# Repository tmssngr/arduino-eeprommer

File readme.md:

# Arduino-Shield to flash EEPROMs

This is an Arduino shield that can be used to read or flash EEPROMs.
I've successfully flashed 28C16 and 28C64.

## Hardware
The schematic you can find [here](kicad/EPROM-Shield.pdf).
It has been created with KiCad 5.1.12.

The 74'595 shift registers are used to set the address lines A0-A12, /CS, /OE and /WE.
The address lines A13 and A14 for 28C128 or 28C256 are only available through jumpers, so only up to 8kB could be flashed in one row.

The EEPROMs data pins are connected via resistors to the arduino pins D0-D7 to prevent problems if the EEPROM and the Arduino accessing these pins as output.
For those arduino boards that use pins D0 and D1 for serial communication, you can use AD0 and AD1 instead.
In that case omit the resistors to D0 and D1, install those to AD0 and AD1, and change the constants `PIN_D0` and `PIN_D1` at the beginning of the [Eprommer595.ino](arduino/Eprommer595/Eprommer595.ino).

Note, you need to solder the pin headers onto the bottom side (in contrast to the below 3D view).

## Software
For simplicity the data to flash should be provided as array content (see [data_jute6k_video.h](arduino/Eprommer595/data_jute6k_video.h)).
Any output is provided over serial communication (9600 baud).

## Todo
- reserve more space around EEPROM to be able to mount a ZIF socket

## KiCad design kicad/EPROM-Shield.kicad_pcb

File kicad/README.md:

# EEPROMmer as Arduino Shield
This is my first attempt to create am EEPROMmer in the form of an Arduino shield.

## Alternative Approaches:
- Arduino-Mega-based: https://github.com/bmpc/arduino_eeprom_programmer
- Very good explanation of steps from breadboard: https://www.youtube.com/watch?v=K88pgWhEb1M

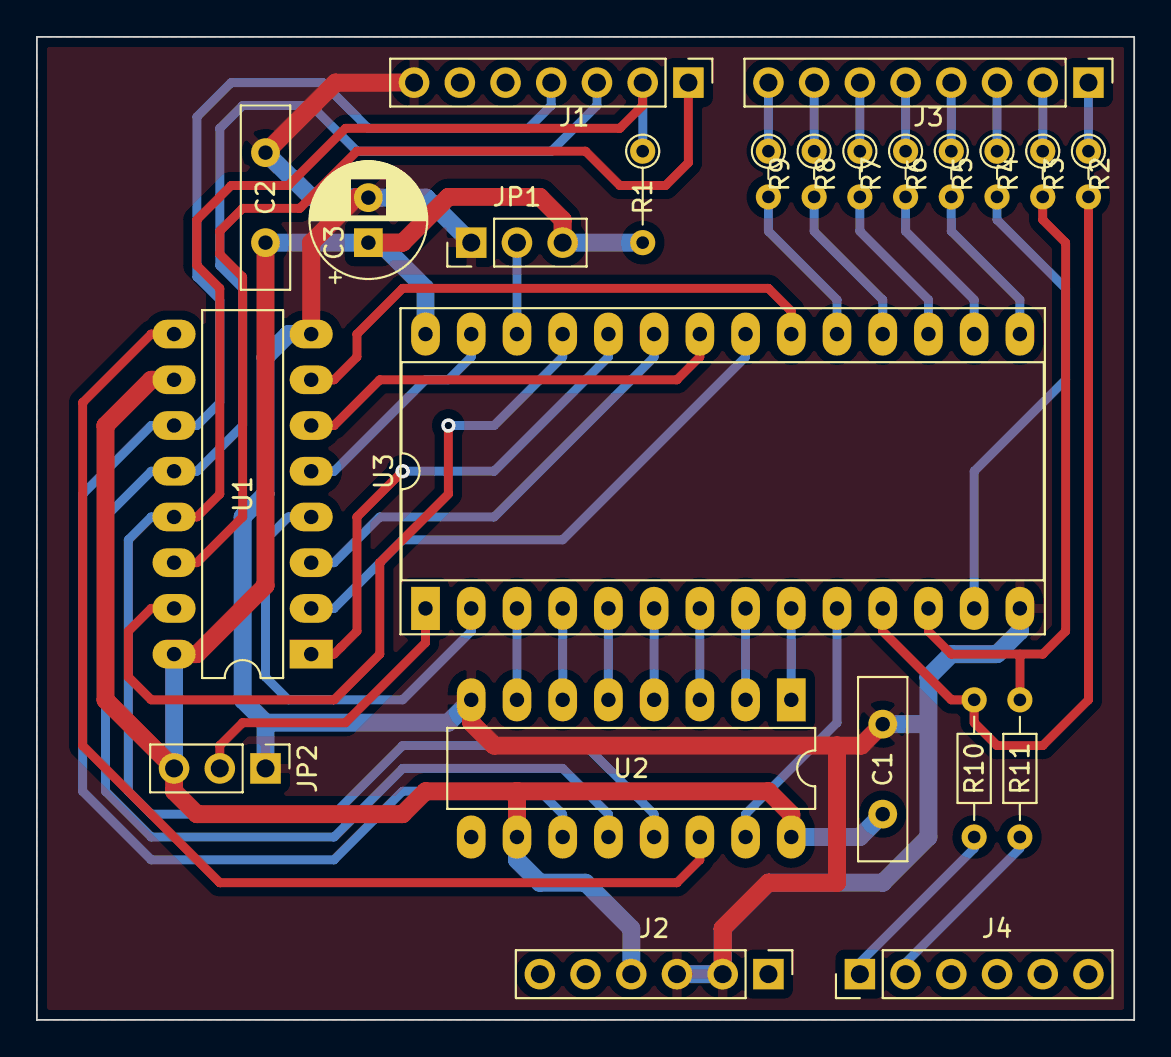
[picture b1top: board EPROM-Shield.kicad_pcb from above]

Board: 2 copper layers, 61.0 x 54.6 mm, 23 parts (0 on the bottom side), 43 nets.

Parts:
C1, C2: 100n; C_Disc_D10.0mm_W2.5mm_P5.00mm
C3: 47u; CP_Radial_D6.3mm_P2.50mm
J1: D8-D13; PinHeader_1x07_P2.54mm_Vertical
J2: Conn_01x06; PinHeader_1x06_P2.54mm_Vertical
J3: D0-D7; PinHeader_1x08_P2.54mm_Vertical
J4: A0-A5; PinHeader_1x06_P2.54mm_Vertical
JP1: A13 1-0; PinHeader_1x03_P2.54mm_Vertical
JP2: A14 1-0; PinHeader_1x03_P2.54mm_Vertical
R1: 10k; R_Axial_DIN0204_L3.6mm_D1.6mm_P5.08mm_Vertical
R2, R3, R4, R5, R6, R7, R8, R9: 510; R_Axial_DIN0204_L3.6mm_D1.6mm_P2.54mm_Vertical
R10, R11: 510; R_Axial_DIN0204_L3.6mm_D1.6mm_P7.62mm_Horizontal
U1, U2: 74LS595; DIP-16_W7.62mm_LongPads
U3: 28C256; DIP-28_W15.24mm_Socket_LongPads

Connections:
/A0: U2.15, U3.10
/A1: U2.1, U3.9
/A2: U2.2, U3.8
/A3: U2.3, U3.7
/A4: U2.4, U3.6
/A5: U2.5, U3.5
/A6: U2.6, U3.4
/A7: U2.7, U3.3
/A8: U1.15, U3.25
/A9: U1.1, U3.24
/A10: U1.2, U3.21
/A11: U1.3, U3.23
/A12: U1.4, U3.2
/A13: JP1.2, U3.26
/A14: JP2.2, U3.1
/AD0: J4.1, R10.1
/AD1: J4.2, R11.1
/CS: U1.7, U3.20
/D0: J3.1, R2.1
/D1: J3.2, R3.1
/D2: J3.3, R4.1
/D3: J3.4, R5.1
/D4: J3.5, R6.1
/D5: J3.6, R7.1
/D6: J3.7, R8.1
/D7: J3.8, R9.1
/OE: U1.6, U3.22
/RCLK: J1.3, U1.12, U2.12
/SER: J1.1, U1.14
/SERCLK: J1.4, U1.11, U2.11
/WE: U1.5, U3.27
/_OE: J1.2, R1.1, U1.13, U2.13
GND: C1.2, C2.2, C3.2, J1.7, J2.2, J2.3, JP1.1, JP2.1, U1.8, U2.8, U3.14
unnamed: R4.2, U3.13
unnamed: R5.2, U3.15
unnamed: R6.2, U3.16
unnamed: R7.2, U3.17
unnamed: R8.2, U3.18
unnamed: R9.2, U3.19
unnamed: R2.2, R10.2, U3.11
unnamed: R3.2, R11.2, U3.12
unnamed: U1.9, U2.14
VCC: C1.1, C2.1, C3.1, J2.4, JP1.3, JP2.3, R1.2, U1.10, U1.16, U2.10, U2.16, U3.28

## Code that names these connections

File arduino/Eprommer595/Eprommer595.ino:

#include "serial_utils.h"
#include "data_jute6k_video.h"
//#include "data_ub8830_jute6k.h"
//#include "data_ub8830_jute6k_modified_keyboard.h"

const uint8_t PIN_SER = 8;
const uint8_t PIN_OE = 9;
const uint8_t PIN_RCLK = 10;
const uint8_t PIN_SERCLK = 11;
const uint8_t PIN_D0 = 0;
const uint8_t PIN_D1 = 1;
const uint8_t PIN_D2 = 2;
const uint8_t PIN_D3 = 3;
const uint8_t PIN_D4 = 4;
const uint8_t PIN_D5 = 5;
const uint8_t PIN_D6 = 6;
const uint8_t PIN_D7 = 7;

const uint8_t DEBUG = 0;

void setup() {
  pinMode(PIN_SER, OUTPUT);
  pinMode(PIN_OE, OUTPUT);
  pinMode(PIN_RCLK, OUTPUT);
  pinMode(PIN_SERCLK, OUTPUT);
  setDataMode(INPUT);
  setAddress_WE_OE_CS(0, 1, 1, 1);

  Serial.begin(9600);
  while (!Serial) {
    // wait
  }

  Serial.println("start" );

  // uncomment the next 2 lines to write and verify the imported DATA array
  //writeData();
  //verifyData();

  printRomContent(0, 0x2000);
}

void loop() {
}

void testWriteRead() {
  for (int i = 0; i < 0x800; i++) {
    write(i, 0xff);
  }

  printRomContent(0, 0x800);
}

uint8_t readData(int address) {
  return pgm_read_byte(DATA + address);
}

void writeData() {
  Serial.println("Writing");

  for (int i = 0; i < DATA_LENGTH; i++) {
    if (i % 16 == 0) {
      if (i > 0) {
        Serial.println();
      }
      serialPrintHex(i, 4);
      Serial.print(" ");
    }

    writeAndVerify(i, readData(i));
  }
}

void verifyData() {
  Serial.println("Verifying");

  int errors = 0;
  for (int i = 0; i < DATA_LENGTH; i++) {
    if (i % 16 == 0) {
      if (i > 0) {
        Serial.println();
      }
      serialPrintHex(i, 4);
    }

    uint8_t readValue = read(i);
    uint8_t expectedValue = readData(i);
    if (readValue != expectedValue) {
      Serial.print(" expected ");
      serialPrintHex(expectedValue, 2);
      Serial.print(" at ");
      serialPrintHex(i, 4);
      Serial.print(", but read ");
      serialPrintHex(readValue, 2);
      Serial.println();
      errors++;
    }

    if (i % 16 == 15 || i + 1 == DATA_LENGTH) {
      Serial.println(" OK");
    }
  }

  if (errors == 0) {
    Serial.println("No errors :)");
  }
  else {
    Serial.print(errors);
    Serial.println(" errors :(");
  }
}

void printRomContent(int start, int end) {
  for (int i = start; i < end; i++) {
    if (i % 16 == 0) {
      if (i > 0) {
        Serial.println();
      }
      serialPrintHex(i, 4);
    }

    Serial.print(" ");

    uint8_t value = read(i);
    serialPrintHex(value, 2);
  }
  Serial.println();
}

void writeAndVerify(uint16_t address, uint8_t value) {
  if (DEBUG == 1) {
    serialPrintHex(address, 4);
    Serial.print(":=");
    serialPrintHex(value, 2);
    Serial.println(">");
  }

  uint8_t existingValue = read(address);
  if (existingValue == value) {
    Serial.print(" ");
    return;
  }

  write(address, value);
  delay(10);

  for (int i = 0; i < 10; i++) {
    uint8_t readValue = read(address);
    if (readValue == value) {
      return;
    }

    Serial.print(".");
  }

  Serial.print("FAILURE at ");
  serialPrintHex(address, 4);
  Serial.print(" - aborting");
  while (true) {
  }
}

void write(uint16_t address, uint8_t value) {
  setAddress_WE_OE_CS(address, 1, 1, 1);
  // In the XL1816 the write cycle is initiated by applying 
  // a logical 0 to both /WE adn /CE while /OE is logical 1.
  // The address inputs are latched into the device on the 
  // falling edge of /WE or /CE (whichever is last) to specify 
  // the address that is to be written.
  setAddress_WE_OE_CS(address, 0, 1, 0);
  setDataMode(OUTPUT);
  writeByte(value);
  // Data on the I/O pins is then latched into the device by
  // bringing either /WE or /CE high.
  setAddress_WE_OE_CS(address, 1, 1, 1);
  // Once the data is latched, the XL2816 will automatically 
  // erase the selected byte and write the new data in less
  // than 10ms.
  // The system is therefore freed to proceed with other operations 
  // while the XL2816 autnomously executes its internal write cycle.
  // The I/O pins will be in a high impedance state while the write
  // operation is in progress with the exception of I/O7 if a read 
  // command is asserted.
  setDataMode(INPUT);
}

void writeByte(uint8_t value) {
  digitalWrite(PIN_D0, (value & 1 << 0) != 0);
  digitalWrite(PIN_D1, (value & 1 << 1) != 0);
  digitalWrite(PIN_D2, (value & 1 << 2) != 0);
  digitalWrite(PIN_D3, (value & 1 << 3) != 0);
  digitalWrite(PIN_D4, (value & 1 << 4) != 0);
  digitalWrite(PIN_D5, (value & 1 << 5) != 0);
  digitalWrite(PIN_D6, (value & 1 << 6) != 0);
  digitalWrite(PIN_D7, (value & 1 << 7) != 0);
}

uint8_t read(uint16_t address) {
  setDataMode(INPUT);
  setAddress_WE_OE_CS(address, 1, 1, 1);
  setAddress_WE_OE_CS(address, 1, 0, 0);
  uint8_t value = readByte();
  setAddress_WE_OE_CS(address, 1, 1, 1);
  return value;
}

uint8_t readByte() {
  return digitalRead(PIN_D0) << 0
       | digitalRead(PIN_D1) << 1
       | digitalRead(PIN_D2) << 2
       | digitalRead(PIN_D3) << 3
       | digitalRead(PIN_D4) << 4
       | digitalRead(PIN_D5) << 5
       | digitalRead(PIN_D6) << 6
       | digitalRead(PIN_D7) << 7;
}

void setDataMode(uint8_t mode) {
  pinMode(PIN_D0, mode);
  pinMode(PIN_D1, mode);
  pinMode(PIN_D2, mode);
  pinMode(PIN_D3, mode);
  pinMode(PIN_D4, mode);
  pinMode(PIN_D5, mode);
  pinMode(PIN_D6, mode);
  pinMode(PIN_D7, mode);
}

void setAddress_WE_OE_CS(uint16_t address, uint8_t we, uint8_t oe, uint8_t cs) {
  uint16_t value = address & 0x1FFF;
  if (we != 0) {
    value |= 0x2000;
  }
  if (oe != 0) {
    value |= 0x4000;
  }
  if (cs != 0) {
    value |= 0x8000;
  }
  shift16(value);
}

void shift16(uint16_t value) {
  if (DEBUG == 1) {
    Serial.print("value = ");
    Serial.println(value, BIN);
  }

  // the serial registers are connected in the wrong order
  // so we need to switch here the bytes

  digitalWrite(PIN_OE, 0);
  digitalWrite(PIN_RCLK, 0);
  digitalWrite(PIN_SERCLK, 0);

  shift8(value);
  shift8(value >> 8);

  digitalWrite(PIN_RCLK, 1);
  delayMicroseconds(1);
  digitalWrite(PIN_RCLK, 0);
  delayMicroseconds(1);
  digitalWrite(PIN_OE, 0);
  delayMicroseconds(1);
}

void shift8(uint16_t value) {
  for (int i = 0; i < 8; i++) {
    const uint8_t bit = (value & 0x80) != 0 ? 1 : 0;

    if (DEBUG == 1) {
      Serial.print(i);
      Serial.print("=");
      Serial.println(bit);
    }

    digitalWrite(PIN_SER, bit);
    delayMicroseconds(1);
    digitalWrite(PIN_SERCLK, 1);
    delayMicroseconds(1);
    digitalWrite(PIN_SERCLK, 0);
    delayMicroseconds(1);

    value <<= 1;
  }
}

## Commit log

2022-06-16 initial import
2022-06-16 add readme.md
2022-06-18 change footprint of EEPROM to one with socket
2022-10-02 data_ub8830_jute6k_modified_keyboard.h
